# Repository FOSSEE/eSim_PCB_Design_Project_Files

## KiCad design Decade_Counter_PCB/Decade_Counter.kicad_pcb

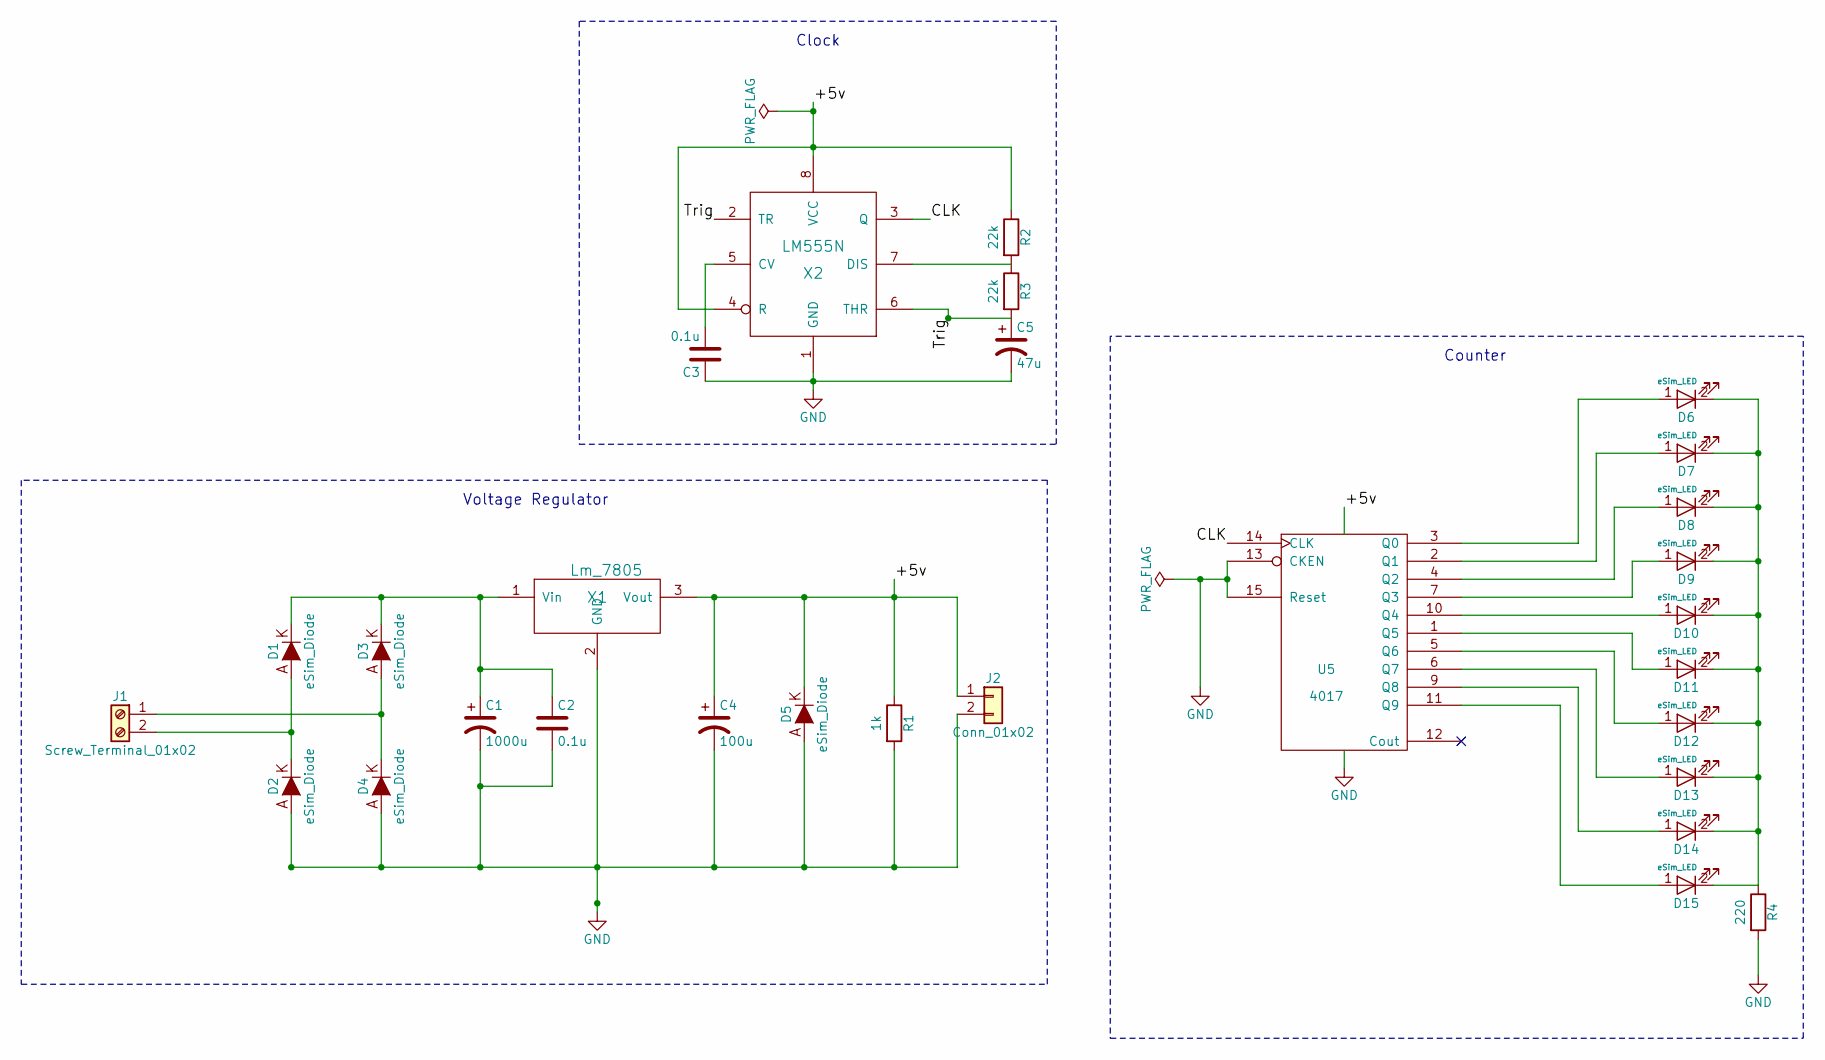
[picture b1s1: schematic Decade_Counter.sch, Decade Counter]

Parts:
C1: 1000u; CP_Radial_D5.0mm_P2.50mm
C2, C3: 0.1u; C_Disc_D3.0mm_W2.0mm_P2.50mm
C4: 100u; CP_Radial_D5.0mm_P2.50mm
C5: 47u; CP_Radial_D5.0mm_P2.50mm
D1, D2, D3, D4, D5: eSim_Diode; D_T-1_P5.08mm_Horizontal
D6, D7, D8, D9, D10, D11, D12, D13, D14, D15: eSim_LED; LED_D5.0mm
J1: Screw_Terminal_01x02; TerminalBlock_Altech_AK300-2_P5.00mm
J2: Conn_01x02; Pin_Header_Straight_1x02_Pitch2.54mm
R1: 1k; R_Axial_DIN0207_L6.3mm_D2.5mm_P10.16mm_Horizontal
R2, R3: 22k; R_Axial_DIN0207_L6.3mm_D2.5mm_P10.16mm_Horizontal
R4: 220; R_Axial_DIN0207_L6.3mm_D2.5mm_P10.16mm_Horizontal
U5: 4017; DIP-16_W7.62mm
X1: Lm_7805; TO-220-3_Vertical
X2: LM555N; DIP-8_W7.62mm

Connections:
/CLK: U5.14 (CLK), X2.3 (Q)
/Trig: C5.1, R3.2, X2.2 (TR), X2.6 (THR)
GND: C1.2, C2.2, C3.1, C4.2, C5.2, D2.1 (A), D4.1 (A), D5.1 (A), J2.2, R1.2, R4.2, U5.8 (VSS), U5.13 (CKEN), U5.15 (Reset), X1.2 (GND), X2.1 (GND)
unnamed: C1.1, C2.1, D1.2 (K), D3.2 (K), X1.1 (Vin)
unnamed: C3.2, X2.5 (CV)
unnamed: D1.1 (A), D2.2 (K), J1.2
unnamed: D3.1 (A), D4.2 (K), J1.1
unnamed: D6.1 (A), U5.3 (Q0)
unnamed: D7.1 (A), U5.2 (Q1)
unnamed: D8.1 (A), U5.4 (Q2)
unnamed: D9.1 (A), U5.7 (Q3)
unnamed: D10.1 (A), U5.10 (Q4)
unnamed: D6.2 (K), D7.2 (K), D8.2 (K), D9.2 (K), D10.2 (K), D11.2 (K), D12.2 (K), D13.2 (K), D14.2 (K), D15.2 (K), R4.1
unnamed: D11.1 (A), U5.1 (Q5)
unnamed: D12.1 (A), U5.5 (Q6)
unnamed: D13.1 (A), U5.6 (Q7)
unnamed: D14.1 (A), U5.9 (Q8)
unnamed: D15.1 (A), U5.11 (Q9)
unnamed: R2.2, R3.1, X2.7 (DIS)
VDD: C4.1, D5.2 (K), J2.1, R1.1, R2.1, U5.16 (VDD), X1.3 (Vout), X2.4 (R), X2.8 (VCC)

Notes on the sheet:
Voltage Regulator
Clock
Counter

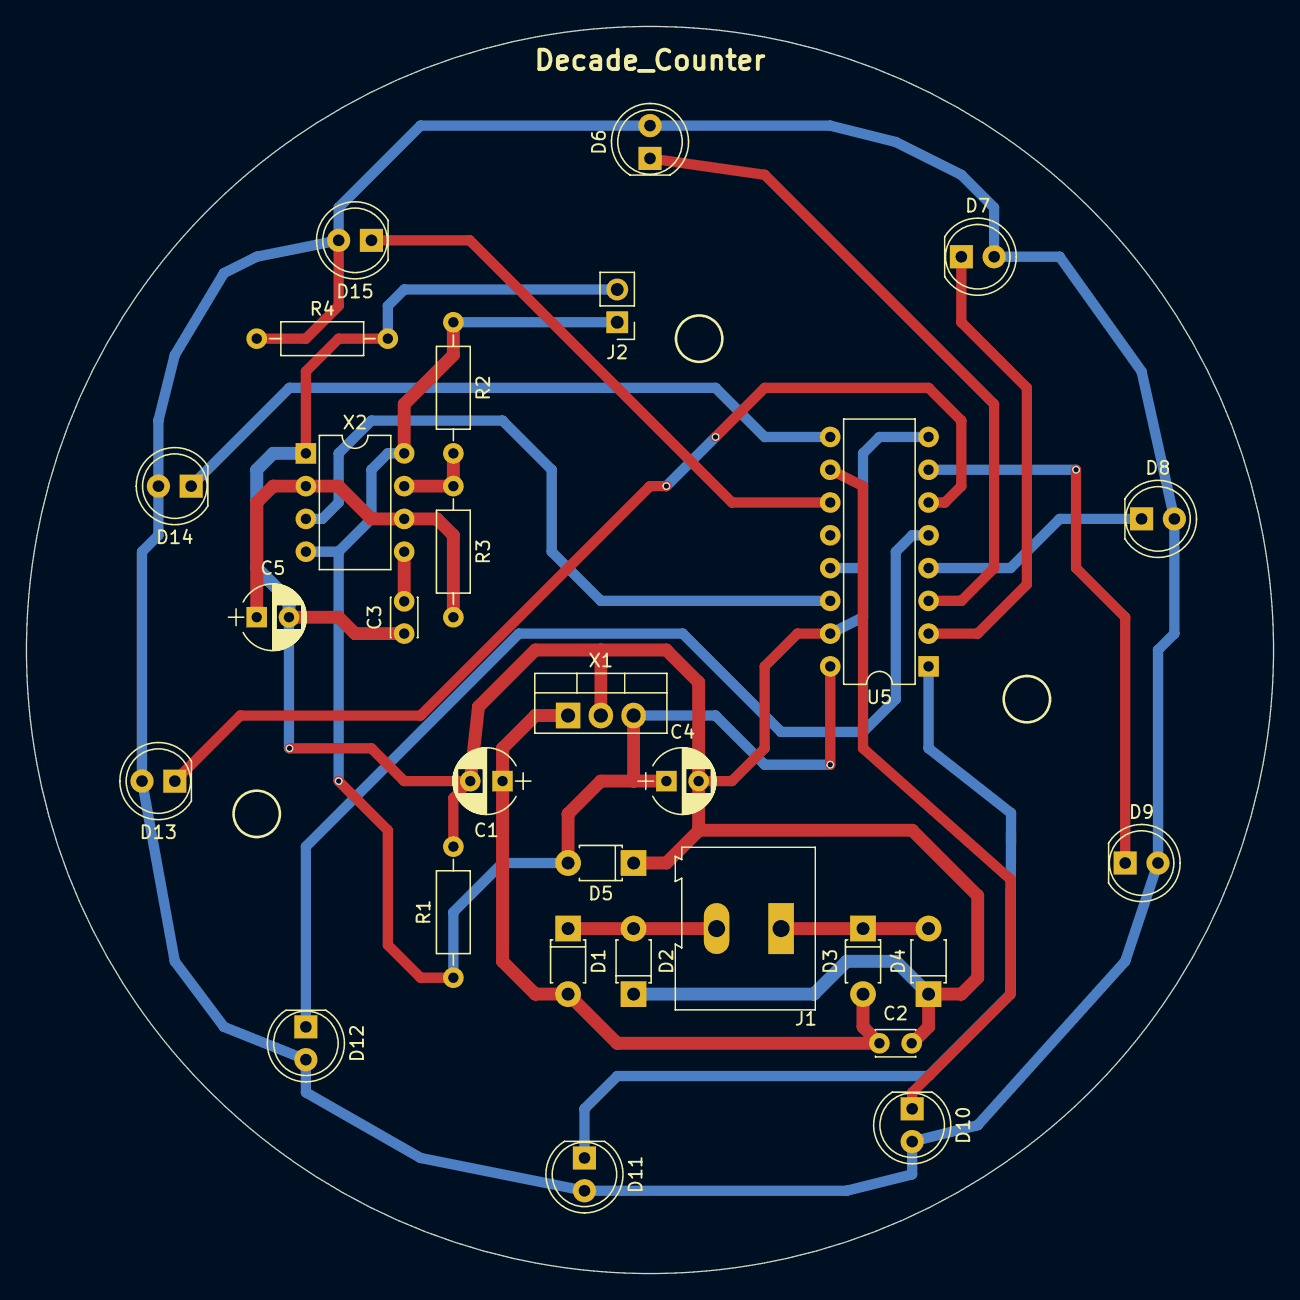
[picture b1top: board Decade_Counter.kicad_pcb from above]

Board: 2 copper layers, 96.7 x 96.7 mm, 29 parts (0 on the bottom side), 20 nets.

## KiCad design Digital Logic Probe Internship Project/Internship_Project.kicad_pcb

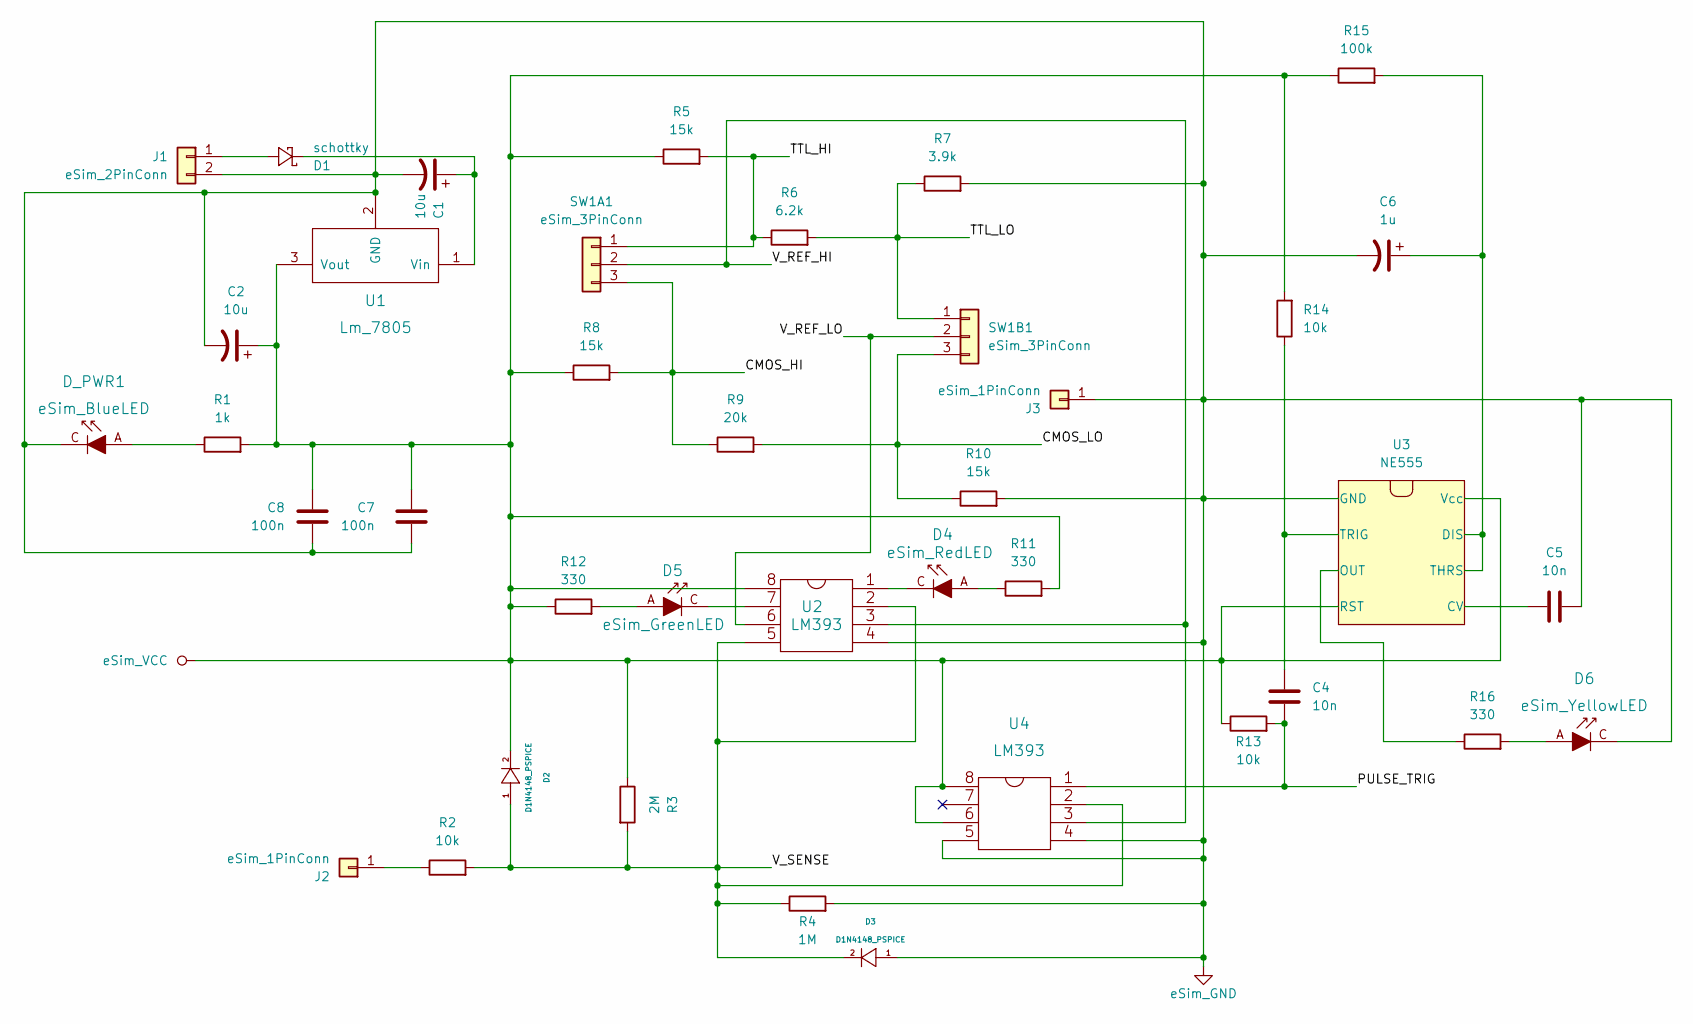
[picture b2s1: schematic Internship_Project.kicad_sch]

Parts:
C1, C2: 10u; CP_Radial_D5.0mm_P2.50mm
C4, C5: 10n; C_Disc_D5.0mm_W2.5mm_P5.00mm
C6: 1u; CP_Radial_D5.0mm_P2.50mm
C7, C8: 100n; C_Disc_D5.0mm_W2.5mm_P5.00mm
D1: schottky; D_DO-41_SOD81_P10.16mm_Horizontal
D2, D3: D1N4148_PSPICE; D_DO-35_SOD27_P7.62mm_Horizontal
D4: eSim_RedLED; LED_D5.0mm
D5: eSim_GreenLED; LED_D5.0mm
D6: eSim_YellowLED; LED_D5.0mm
D_PWR1: eSim_BlueLED; LED_D5.0mm
J1: eSim_2PinConn; PinHeader_1x02_P2.54mm_Vertical
J2, J3: eSim_1PinConn; PinHeader_1x01_P2.54mm_Vertical
R1: 1k; R_Axial_DIN0207_L6.3mm_D2.5mm_P10.16mm_Horizontal
R2, R13, R14: 10k; R_Axial_DIN0207_L6.3mm_D2.5mm_P10.16mm_Horizontal
R3: 2M; R_Axial_DIN0207_L6.3mm_D2.5mm_P10.16mm_Horizontal
R4: 1M; R_Axial_DIN0207_L6.3mm_D2.5mm_P10.16mm_Horizontal
R5, R8, R10: 15k; R_Axial_DIN0207_L6.3mm_D2.5mm_P10.16mm_Horizontal
R6: 6.2k; R_Axial_DIN0207_L6.3mm_D2.5mm_P10.16mm_Horizontal
R7: 3.9k; R_Axial_DIN0207_L6.3mm_D2.5mm_P10.16mm_Horizontal
R9: 20k; R_Axial_DIN0207_L6.3mm_D2.5mm_P10.16mm_Horizontal
R11, R12, R16: 330; R_Axial_DIN0207_L6.3mm_D2.5mm_P10.16mm_Horizontal
R15: 100k; R_Axial_DIN0207_L6.3mm_D2.5mm_P10.16mm_Horizontal
SW1A1, SW1B1: eSim_3PinConn; PinHeader_1x03_P2.54mm_Vertical
U1: Lm_7805; TO-220-3_Vertical
U2, U4: LM393; DIP-8_W7.62mm
U3: NE555; DIP-8_W7.62mm

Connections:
/CMOS_HI: R8.2, R9.1, SW1A1.3
/CMOS_LO: R9.2, R10.1, SW1B1.3
/PULSE_TRIG: C4.2, R13.2, U4.4 (1)
/TTL_HI: R5.2, R6.1, SW1A1.1
/TTL_LO: R6.2, R7.1, SW1B1.1
/V_REF_HI: SW1A1.2, U2.2 (3), U4.2 (3)
/V_REF_LO: SW1B1.2, U2.7 (6)
/V_SENSE: D2.1, D3.2, R2.2, R3.2, R4.1, U2.3 (2), U2.6 (5), U4.3 (2)
GND: C1.2, C2.2, C5.2, C6.2, C7.2, C8.2, D3.1, D6.C, D_PWR1.C, J1.2, J3.1, R4.2, R7.2, R10.2, U1.2 (GND), U2.5 (4), U3.1 (GND), U4.5 (4), U4.6 (5)
unnamed: C1.1, D1.2 (-), U1.1 (Vin)
unnamed: C4.1, R14.1, U3.2 (TRIG)
unnamed: C5.1, U3.5 (CV)
unnamed: C6.1, R15.2, U3.6 (THRS), U3.7 (DIS)
unnamed: D1.1 (+), J1.1
unnamed: D4.A, R11.1
unnamed: D4.C, U2.4 (1)
unnamed: D5.A, R12.2
unnamed: D5.C, U2.8 (7)
unnamed: D6.A, R16.2
unnamed: D_PWR1.A, R1.1
unnamed: J2.1, R2.1
unnamed: R16.1, U3.3 (OUT)
VCC: C2.1, C7.1, C8.1, D2.2, R1.2, R3.1, R5.1, R8.1, R11.2, R12.1, R13.1, R14.2, R15.1, U1.3 (Vout), U2.1 (8), U3.4 (RST), U3.8 (Vcc), U4.1 (8), U4.7 (6)

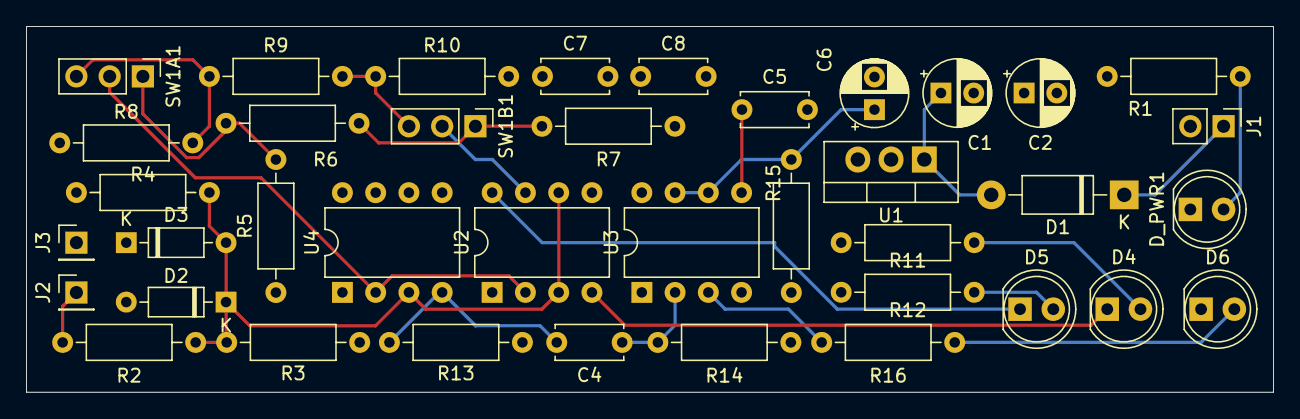
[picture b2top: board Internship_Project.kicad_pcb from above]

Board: 4 copper layers, 95.2 x 27.9 mm, 39 parts (0 on the bottom side), 23 nets.

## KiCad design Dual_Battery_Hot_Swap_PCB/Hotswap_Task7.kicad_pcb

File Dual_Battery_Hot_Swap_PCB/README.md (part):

# Dual-Battery Automatic Hot-Swap Circuit (2-Layer PCB)

A compact **Dual-Battery Automatic Hot-Swap Circuit** PCB designed for a **16 V, 5 A load** using **eSim 2.5 / KiCad 6.0.11**. The board connects two battery inputs (`J1_BAT1` and `J4_BAT2`) to a shared load output (`J3_LOAD1`) with voltage sensing, comparator control, MOSFET switching, and a bulk hold-up capacitor (`C4`) so power to the load stays smooth during battery switching.

**Author:** MD Hazijul Haque

**Program:** FOSSEE eSim Winter Internship 2026 (Task 7)

**Project Folder:** `Dual_Battery_Hot_Swap_PCB/` (`Hotswap_Task7`)

**Project Report:** [Hotswap_Task7_Report.pdf](https://github.com/Hazijul/eSim_PCB_Design_Hot_Swap_File/blob/main/Dual_Battery_Hot_Swap_PCB/Hotswap_Task7_Report.pdf)

**Repository & PR:** [Hazijul/eSim_PCB_Design_Hot_Swap_File](https://github.com/Hazijul/eSim_PCB_Design_Hot_Swap_File/tree/main/Dual_Battery_Hot_Swap_PCB) (`Dual_Battery_Hot_Swap_PCB/`) — [Pull Request #49 on FOSSEE/eSim_PCB_Design_Project_Files](https://github.com/FOSSEE/eSim_PCB_Design_Project_Files/pull/49)
---

## Hardware Specifications

| Parameter | Specification |
| :--- | :--- |
| **Voltage & Current Rating** | **16 V**, **5 A** load capability |
| **Battery Inputs** | Dual battery terminals (`J1_BAT1`, `J4_BAT2`) |
| **Load Output** | Shared load terminal (`J3_LOAD1`) |
| **Voltage Comparator** | **LM393** dual comparator (`U2A`, `U2B`, `U2C` power/ground) with **2.5 V** reference (`D1`) |
| **Power Switching MOSFETs** | Back-to-back P-channel MOSFETs (`Q1–Q4`, `Si4425BDY` / `AO3401A` in KiCad 6) |
| **Gate Drive MOSFETs** | N-channel MOSFET switches (`Q5–Q7`, `2N7002`) |
| **Hold-Up & Sense Parts** | **470 µF** bulk hold-up capacitor (`C4`), path/sense resistors (`R1`, `R2`), divider/bias network (`R4–R9`), indicators (`D2`, `D3`, `D4`, `R3`) |
| **PCB Stackup & Size** | **50 mm × 50 mm**, **2-Layer FR4** (`F.Cu` & `B.Cu`) |
| **Verification Tool** | eSim 2.5 / KiCad 6.0.11 (`ERC.rpt` & `DRC.rpt` with 0 errors) |

---

## Schematic Explanation

The schematic (`Hotswap_Task7.kicad_sch`) is divided into clear functional sections so anyone reading the circuit can see how battery inputs are sensed, how switching decisions are made, and how power reaches the load.

### 1. Dual Battery Inputs & Power Path
- **Two Battery Channels (`J1_BAT1` and `J4_BAT2`):** Two screw-terminal battery inputs feed into the hot-swap circuit so the system can draw from dual battery sources.
- **Series Resistors & Indicators (`R1`, `R2`, `D2`, `D3`):** Each battery branch includes its path/sense resistor (`R1`, `R2` at `1.0R`) and status LED (`D2`, `D3`) so you can tell at a glance which battery path is active or present.
- **Shared Load Output (`J3_LOAD1`):** Both battery paths feed into the main load output (`J3_LOAD1`) along with a load/status indicator branch (`R3` and `D4`).

### 2. Voltage Sensing & LM393 Comparator Logic
- **Reference & Voltage Divider (`D1`, `R4`, `R5`, `R6`):** A **2.5 V** reference (`D1`) and resistor divider network (`R4`, `R5`, `R6`) provide a steady comparison threshold and scaled voltage input (`COMP_IN+` / `COMP_IN-`) for monitoring battery voltage.
- **Comparator & Biasing (`U2A`, `U2B`, `U2C`, `R7`, `R8`, `R9`):** The **LM393** dual comparator compares the sensed voltage against the reference/threshold and drives the comparator output (`COMP_OUT`) with supporting bias and feedback resistors (`R7`, `R8`, `R9`).

### 3. Gate Drive & Back-to-Back MOSFET Switching
- **N-Channel Gate Drivers (`Q5–Q7`, `2N7002`):** The `2N7002` N-channel MOSFETs (`Q5`, `Q6`, `Q7`) act as small control switches driven by the comparator/logic signals (`COMP_OUT`, `COMP_INV`) to control the gate lines (`GATE1`, `GATE2`) of the main power MOSFETs.
- **Back-to-Back P-Channel MOSFETs (`Q1–Q4`):** Four P-channel MOSFETs (`Q1–Q2` on one path and `Q3–Q4` on the other) are arranged back-to-back. Using back-to-back MOSFETs blocks unwanted reverse current flow through the internal body diode when a channel is turned off or when one battery has a different voltage than the other.

### 4. Bulk Hold-Up Capacitor (`C4`)
- **Smoothing During Switchover:** A **470 µF** bulk capacitor (`C4`) sits on the output side toward the load (`J3_LOAD1`). When switching between battery sources or hot-swapping a pack, `C4` helps buffer brief current dips so the load sees a steadier voltage transition.

### Circuit Schematic

---

## PCB Design & Layout Explanation

The 2-layer PCB (`Hotswap_Task7.kicad_pcb`) fits everything into a compact **50 mm × 50 mm** square board while keeping high-current paths clear and organized.

### 1. Compact 50 mm × 50 mm Board Layout
- **Connectors & Accessibility:** Battery connectors (`J1_BAT1`, `J4_BAT2`) and the load output (`J3_LOAD1`) are placed cleanly around the board edges so wiring a 16 V, 5 A setup is straightforward.
- **Logical Grouping:** Power path components (`J1_BAT1`, `J4_BAT2`, `J3_LOAD1`, `Q1–Q4`, `R1`, `R2`, `C4`) sit close together along the high-current path, while the `LM393` comparator (`U2`), reference/divider resistors, and `2N7002` drivers (`Q5–Q7`) are grouped neatly nearby.

### 2. Handling 5 A Current Safely on a 2-Layer Board
A **5 A** load current on a 2-layer board requires wider, shorter copper paths than low-current signal traces:
- **Wider High-Current Copper:** The battery-to-MOSFET-to-load (`VOUT`) and ground return paths use wider traces/copper areas to reduce resistance, voltage drop, and heating at 5 A.
- **Short Loops:** Keeping `Q1–Q4`, `R1`/`R2`, and the `470 µF` capacitor (`C4`) close to `J1_BAT1`, `J4_BAT2`, and `J3_LOAD1` keeps high-current loops tight and tidy.

### 3. Separating Comparator & Gate Signals from High-Current Paths
- **Clean Sensing & Control:** Voltage-divider and comparator lines carry small reference/sense signals, while `Q5–Q7` drive `GATE1` and `GATE2`. Routing these cleanly away from heavy current paths reduces unwanted noise pickup.
- **Ground Reference:** A broad ground copper fill on the board gives return currents a low-resistance path and keeps reference measurements consistent.

### 4. Design Verification (ERC & DRC)
Two checks in eSim 2.5 / KiCad 6.0.11 verify the schematic and PCB before release:
- **Electrical Rules Check (`ERC.rpt`):** Confirms schematic connections and symbol references have **0 errors**.
- **Design Rules Check (`DRC.rpt`):** Confirms physical track widths, clearances, drill/pad rules, and copper pours on the 50 mm × 50 mm board pass with **0 errors**.

### Quick Summary of Circuit & Layout Blocks

| Block / Section | Key Parts | Role in the Circuit |
| :--- | :--- | :--- |
| **Battery & Load Terminals** | `J1_BAT1`, `J4_BAT2`, `J3_LOAD1` | Connects Battery 1, Battery 2, and the 16 V / 5 A load |
| **Voltage Sense & Comparator** | `LM393` (`U2`), `D1` (2.5 V), `R4–R9` | Monitors battery voltage against threshold/reference and drives control logic |
| **Gate Drive & Power Switches** | `Q1–Q4` (PMOS), `Q5–Q7` (`2N7002`), `R1`, `R2` | Switches battery paths smoothly with back-to-back reverse-blocking protection |
| **Hold-Up & Indicators** | `C4` (`470 µF`), `D2`, `D3`, `D4`, `R3` | Supports load voltage during switchover and shows status visually |

### 2-Layer PCB Layout (Front, Back & Both Layers)

### 3D PCB Render (Front & Back)

---

## Verification Results (ERC & DRC)

Both schematic ERC and PCB DRC were run and verified with **0 errors** in eSim 2.5 / KiCad 6.0.11, with full text reports saved as `ERC.rpt` and `DRC.rpt` inside this folder.

### Electrical Rules Check (ERC)

### Design Rules Check (DRC)

---

## System Working Flow

```mermaid
flowchart TD
    subgraph Inputs["Dual Battery Inputs"]
        B1["Battery 1 (J1_BAT1)<br/>R1 (1.0R) & Indicator D2"]
        B2["Battery 2 (J4_BAT2)<br/>R2 (1.0R) & Indicator D3"]
    end

    subgraph Control["Voltage Sense & Comparator Control"]
        SENSE["Voltage Divider & 2.5V Ref<br/>(D1, R4, R5, R6)"] --> CMP["LM393 Dual Comparator (U2)<br/>& Bias/Feedback (R7, R8, R9)"]
        CMP --> DRV["2N7002 Gate Drivers (Q5–Q7)<br/>GATE1 & GATE2 Control"]
    end

    B1 -. "Voltage Sensing" .-> SENSE
    B2 -. "Voltage Sensing" .-> SENSE

    subgraph Switching["Back-to-Back PMOS Hot-Swap Stage"]
        B1 --> PMOS1["Q1–Q2 Back-to-Back PMOS<br/>(Si4425BDY / AO3401A)"]
        B2 --> PMOS2["Q3–Q4 Back-to-Back PMOS<br/>(Si4425BDY / AO3401A)"]
        DRV -. "Gate Drive" .-> PMOS1
        DRV -. "Gate Drive" .-> PMOS2
    end

    subgraph Output["Hold-Up & Load Output (16V, 5A)"]
        PMOS1 --> BUS["Common Output Bus"]
        PMOS2 --> BUS
        BUS --> CAP["470 µF Bulk Hold-Up Cap (C4)"]
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
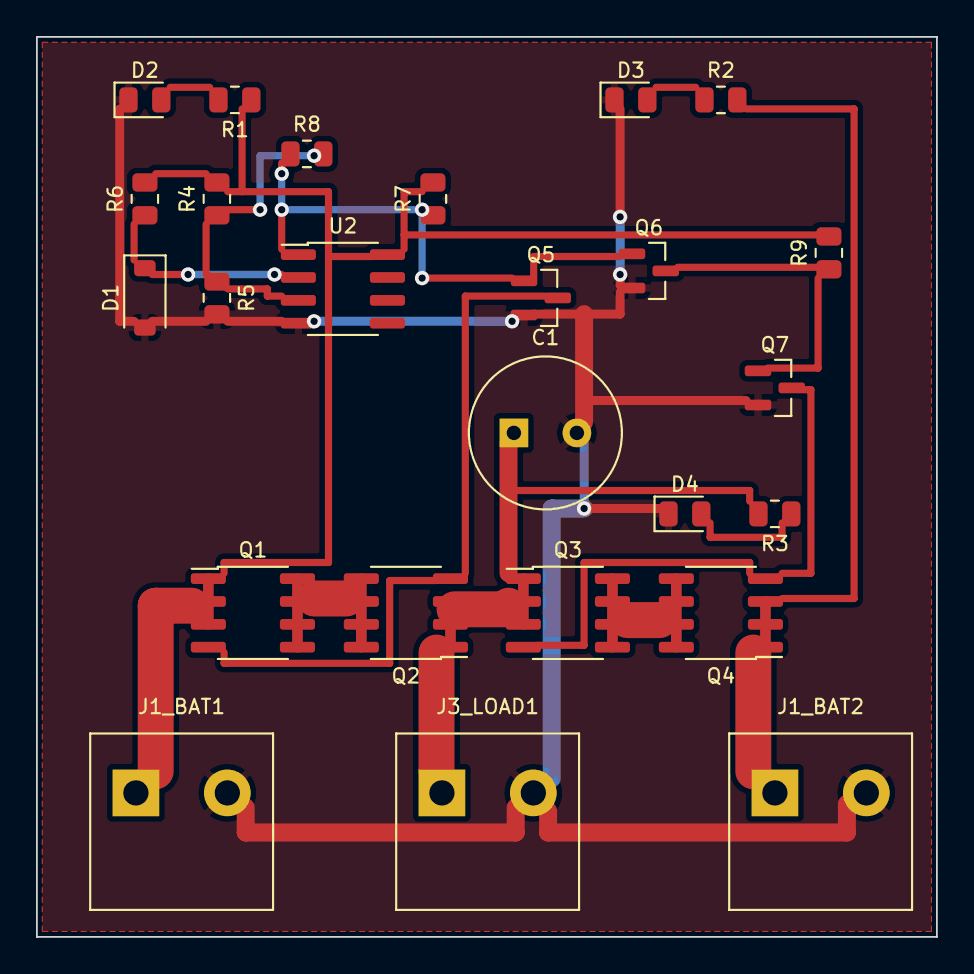
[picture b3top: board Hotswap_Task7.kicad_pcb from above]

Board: 2 copper layers, 50.0 x 50.0 mm, 25 parts (0 on the bottom side), 15 nets.

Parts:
C1: 470uF; CP_Radial_D8.0mm_P3.50mm
D1: 2.5V; D_SOD-123
D2, D3, D4: LED; LED_0805_2012Metric
J1_BAT1, J1_BAT2, J3_LOAD1: Screw_Terminal_01x02; TerminalBlock_Phoenix_MKDS-1,5-2-5.08_1x02_P5.08mm_Horizont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
Q1, Q2, Q3, Q4: Si4425BDY; SOIC-8_3.9x4.9mm_P1.27mm
Q5, Q6, Q7: 2N7002; SOT-23
R1, R2, R3: 1.8k; R_0805_2012Metric
R4: 49.9k; R_0805_2012Metric
R5, R6, R7, R9: 10k; R_0805_2012Metric
R8: 1.1Meg; R_0805_2012Metric
U2: LM393; SOIC-8_3.9x4.9mm_P1.27mm

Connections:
COMP_IN+: R4.1, R5.2, R8.2, U2.3
COMP_IN-: D1.1, R6.1, U2.2
COMP_INV: Q6.3, Q7.1, R9.1
COMP_OUT: Q5.1, Q6.1, R7.1, R8.1, U2.1
GATE1: Q1.4, Q2.4, Q5.3
GATE2: Q3.4, Q4.4, Q7.3
GND: C1.2, D1.2, D2.1, D3.1, D4.1, J1_BAT1.2, J1_BAT2.2, J3_LOAD1.2, Q5.2, Q6.2, Q7.2, R5.1, U2.4
unnamed: D2.2, R1.2
unnamed: D3.2, R2.1
unnamed: D4.2, R3.1
unnamed: Q1.5, Q1.6, Q1.7, Q1.8, Q2.5, Q2.6, Q2.7, Q2.8
unnamed: Q3.5, Q3.6, Q3.7, Q3.8, Q4.5, Q4.6, Q4.7, Q4.8
VOUT: C1.1, J3_LOAD1.1, Q2.1, Q2.2, Q2.3, Q3.1, Q3.2, Q3.3, R3.2
V_BAT1: J1_BAT1.1, Q1.1, Q1.2, Q1.3, R1.1, R4.2, R6.2, R7.2, R9.2, U2.8
V_BAT2: J1_BAT2.1, Q4.1, Q4.2, Q4.3, R2.2

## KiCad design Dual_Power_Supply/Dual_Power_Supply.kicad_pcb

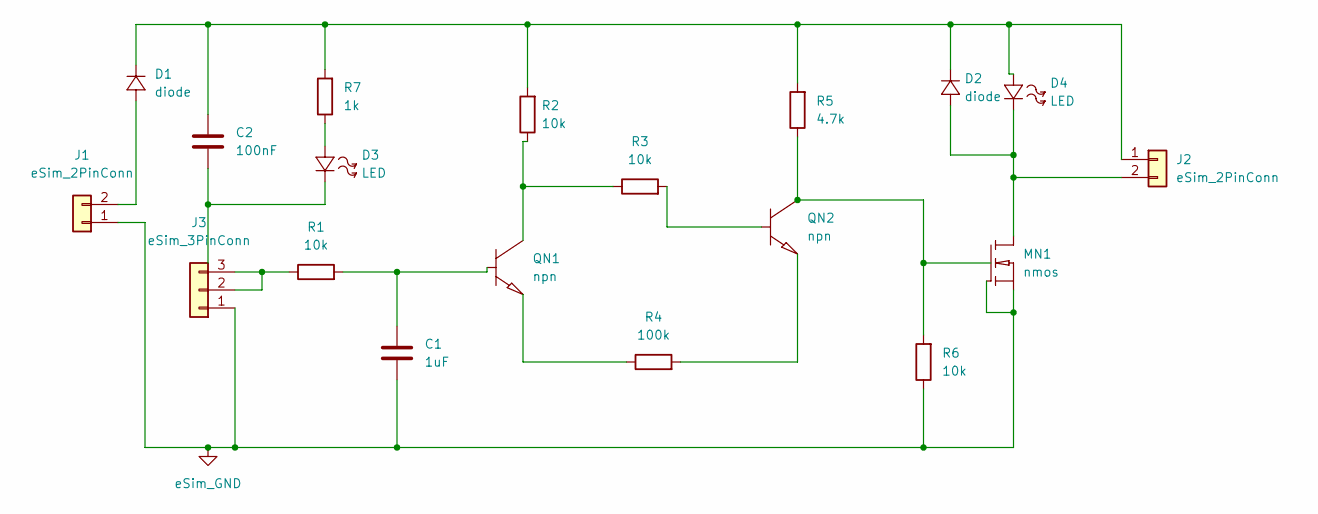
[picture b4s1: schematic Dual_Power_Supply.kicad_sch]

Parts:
C1: 1uF; C_Disc_D5.0mm_W2.5mm_P5.00mm
C2: 100nF; C_Disc_D5.0mm_W2.5mm_P5.00mm
D1, D2: diode; D_DO-41_SOD81_P10.16mm_Horizontal
D3, D4: LED; LED_D5.0mm
J1, J2: eSim_2PinConn; PinHeader_1x02_P2.54mm_Vertical
J3: eSim_3PinConn; PinHeader_1x03_P2.54mm_Vertical
MN1: nmos; TO-220-3_Vertical
QN1, QN2: npn; TO-92_Inline
R1, R2, R3, R6: 10k; R_Axial_DIN0207_L6.3mm_D2.5mm_P10.16mm_Horizontal
R4: 100k; R_Axial_DIN0207_L6.3mm_D2.5mm_P10.16mm_Horizontal
R5: 4.7k; R_Axial_DIN0207_L6.3mm_D2.5mm_P10.16mm_Horizontal
R7: 1k; R_Axial_DIN0207_L6.3mm_D2.5mm_P10.16mm_Horizontal

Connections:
GND: C1.2, J1.1, J3.1, MN1.2 (G), MN1.3 (S), R6.1
unnamed: D3.1 (+), R7.1
unnamed: C2.2, D3.2 (-)
unnamed: D2.1 (+), D4.2 (-), J2.2, MN1.1 (D)
unnamed: D1.1 (+), J1.2
unnamed: QN1.3 (E), R4.1
unnamed: QN2.1 (C), R5.1, R6.2
unnamed: QN2.3 (E), R4.2
unnamed: J3.2, J3.3, R1.1
unnamed: C1.1, QN1.2 (B), R1.2
unnamed: QN1.1 (C), R2.1, R3.1
unnamed: QN2.2 (B), R3.2
unnamed: C2.1, D1.2 (-), D2.2 (-), D4.1 (+), J2.1, R2.2, R5.2, R7.2

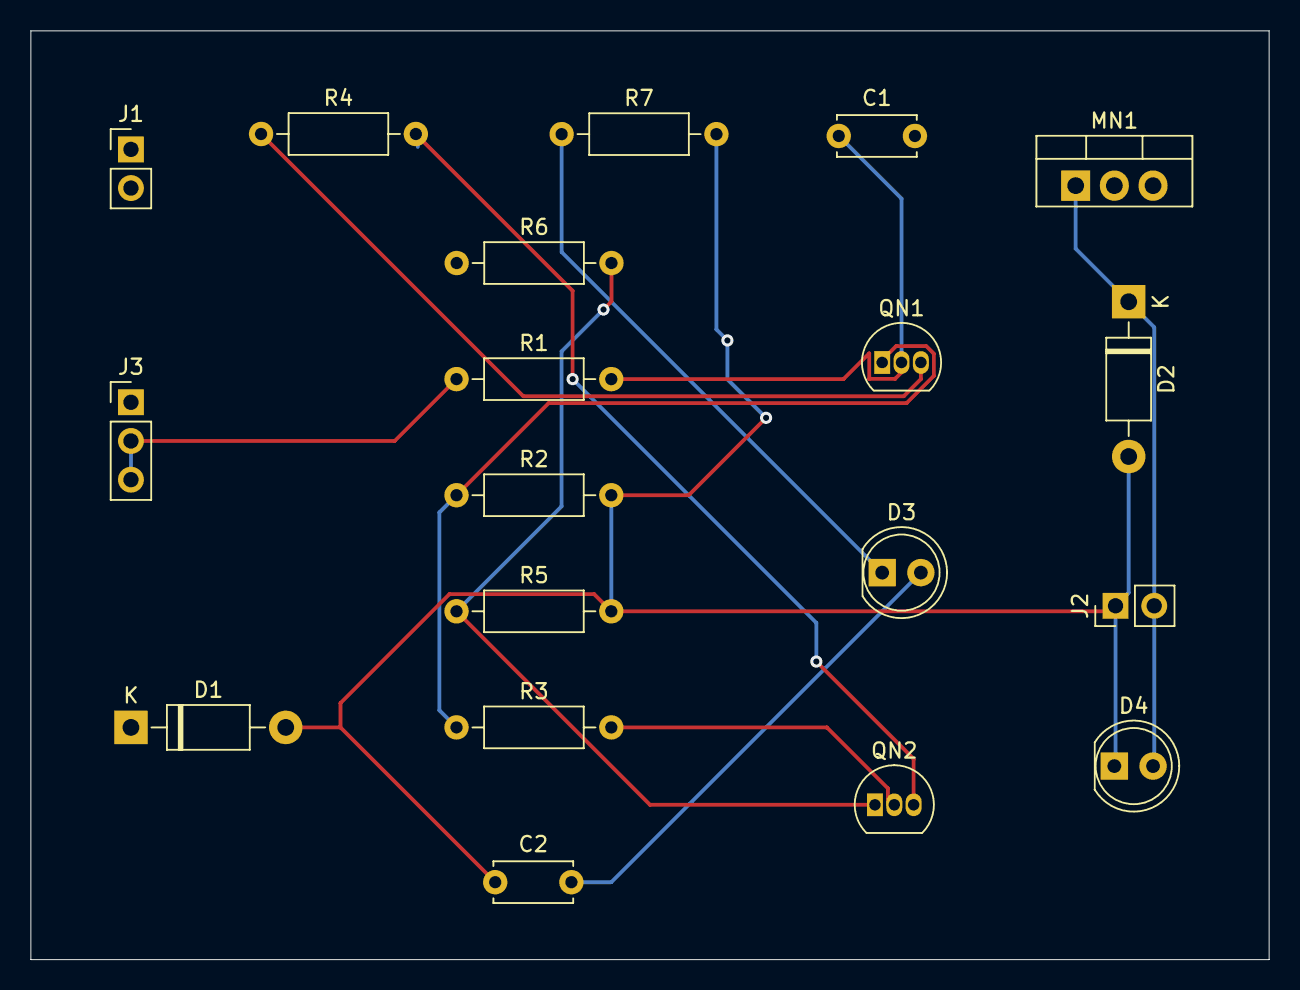
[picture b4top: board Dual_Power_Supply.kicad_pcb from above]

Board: 4 copper layers, 81.3 x 61.0 mm, 19 parts (0 on the bottom side), 13 nets.

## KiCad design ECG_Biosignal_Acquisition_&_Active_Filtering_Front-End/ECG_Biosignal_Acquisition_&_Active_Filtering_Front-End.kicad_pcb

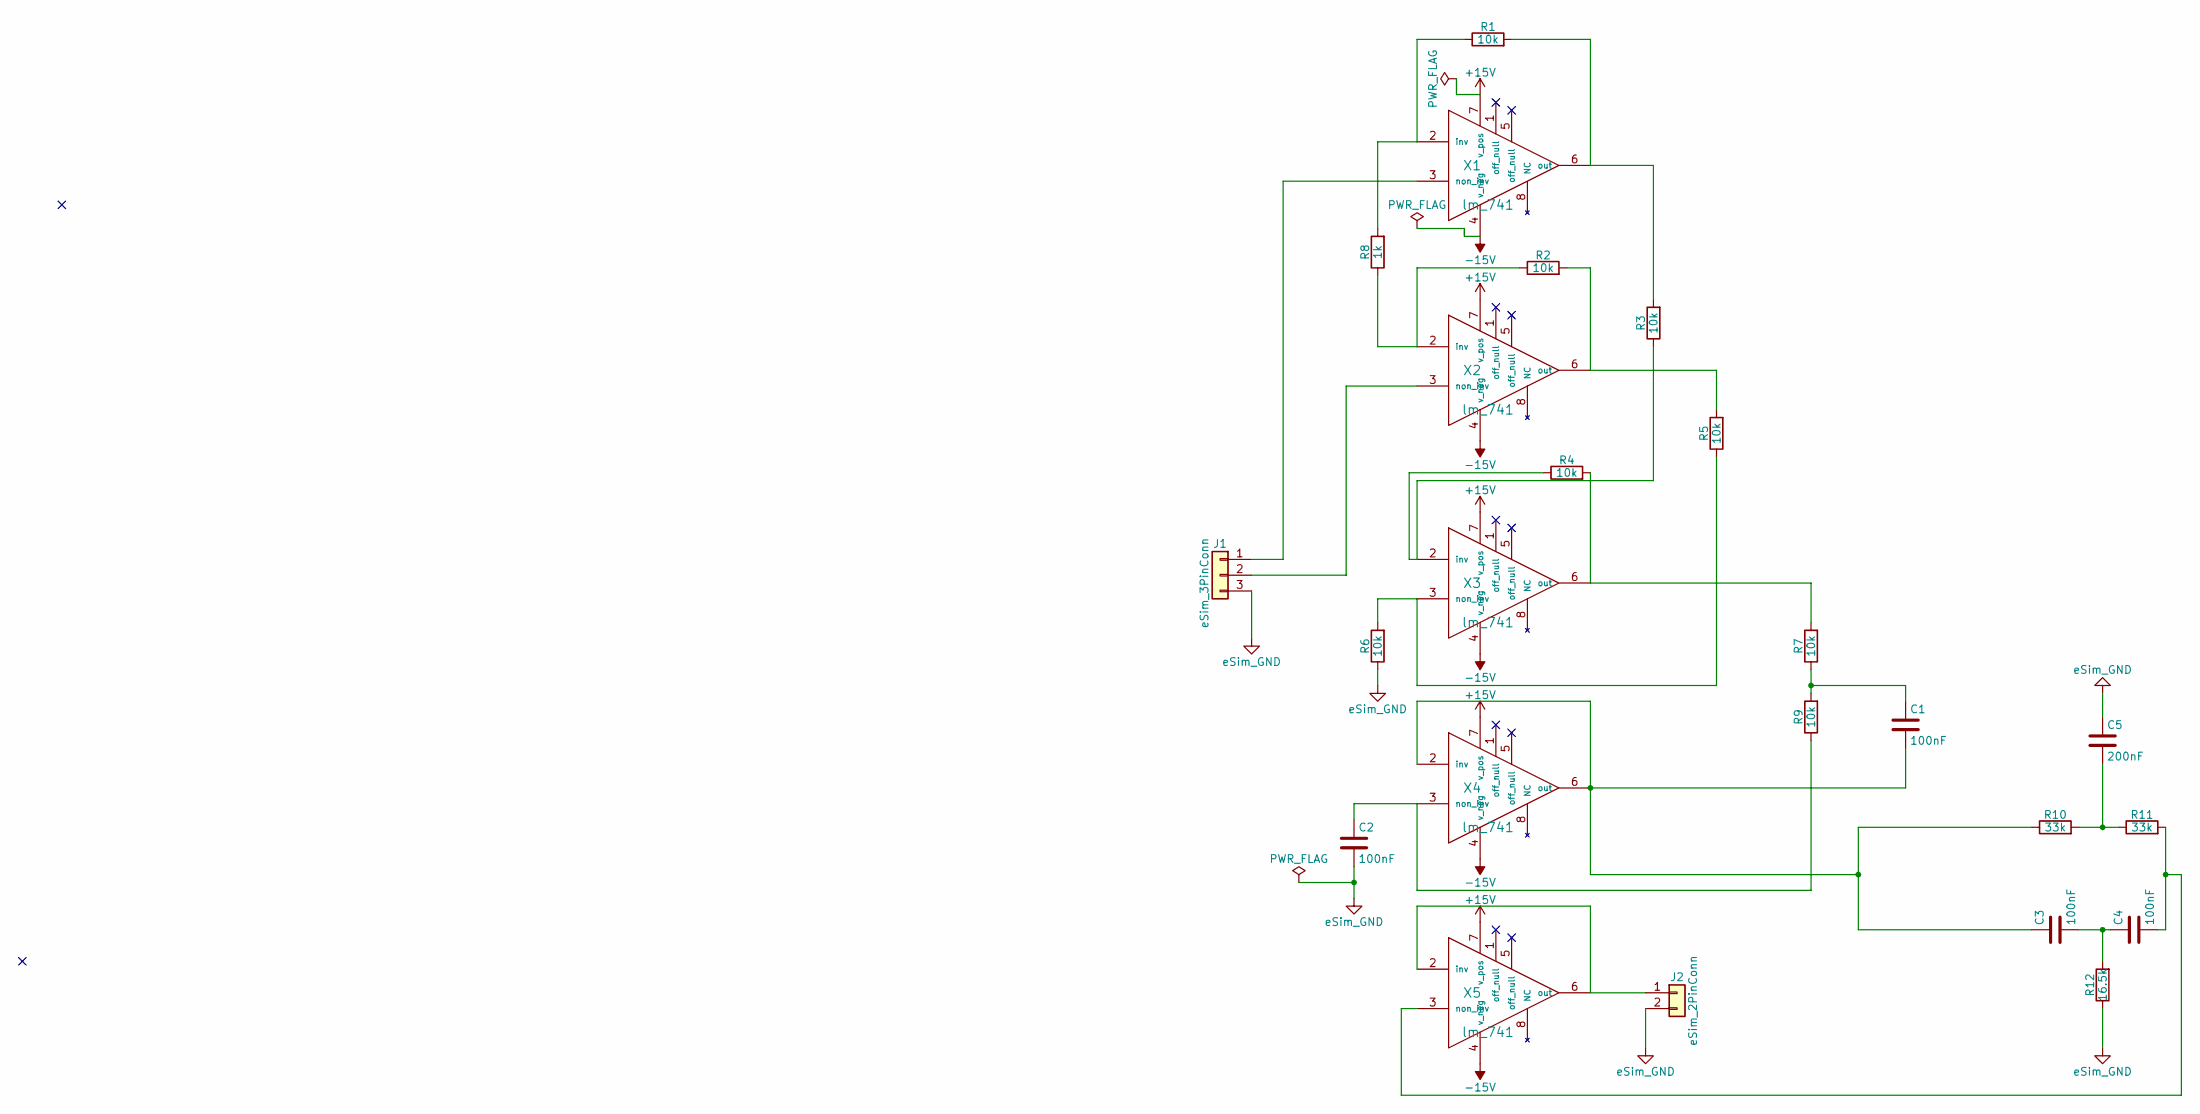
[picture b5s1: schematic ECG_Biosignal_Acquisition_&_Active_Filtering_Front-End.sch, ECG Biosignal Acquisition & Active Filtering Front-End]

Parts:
C1, C2, C3, C4: 100nF; C_Disc_D5.0mm_W2.5mm_P5.00mm
C5: 200nF; C_Disc_D5.0mm_W2.5mm_P5.00mm
J1: eSim_3PinConn; Pin_Header_Straight_1x03_Pitch2.54mm
J2: eSim_2PinConn; Pin_Header_Straight_1x02_Pitch2.54mm
R1, R2, R3, R4, R5, R6, R7, R9: 10k; R_Axial_DIN0207_L6.3mm_D2.5mm_P7.62mm_Horizontal
R8: 1k; R_Axial_DIN0207_L6.3mm_D2.5mm_P7.62mm_Horizontal
R10, R11: 33k; R_Axial_DIN0207_L6.3mm_D2.5mm_P7.62mm_Horizontal
R12: 16.5k; R_Axial_DIN0207_L6.3mm_D2.5mm_P7.62mm_Horizontal
X1, X2, X3, X4, X5: lm_741; DIP-8_W7.62mm

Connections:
+15V: X1.7 (v_pos), X2.7 (v_pos), X3.7 (v_pos), X4.7 (v_pos), X5.7 (v_pos)
-15V: X1.4 (v_neg), X2.4 (v_neg), X3.4 (v_neg), X4.4 (v_neg), X5.4 (v_neg)
GND: C2.2, C5.1, J1.3, J2.2, R6.1, R12.1
unnamed: C1.1, R7.1, R9.2
unnamed: C1.2, C3.1, R10.1, X4.2 (inv), X4.6 (out)
unnamed: C2.1, R9.1, X4.3 (non_inv)
unnamed: C3.2, C4.1, R12.2
unnamed: C4.2, R11.2, X5.3 (non_inv)
unnamed: C5.2, R10.2, R11.1
unnamed: J1.1, X1.3 (non_inv)
unnamed: J1.2, X2.3 (non_inv)
unnamed: J2.1, X5.2 (inv), X5.6 (out)
unnamed: R1.1, R8.2, X1.2 (inv)
unnamed: R1.2, R3.2, X1.6 (out)
unnamed: R2.1, R8.1, X2.2 (inv)
unnamed: R2.2, R5.2, X2.6 (out)
unnamed: R3.1, R4.1, X3.2 (inv)
unnamed: R4.2, R7.2, X3.6 (out)
unnamed: R5.1, R6.2, X3.3 (non_inv)

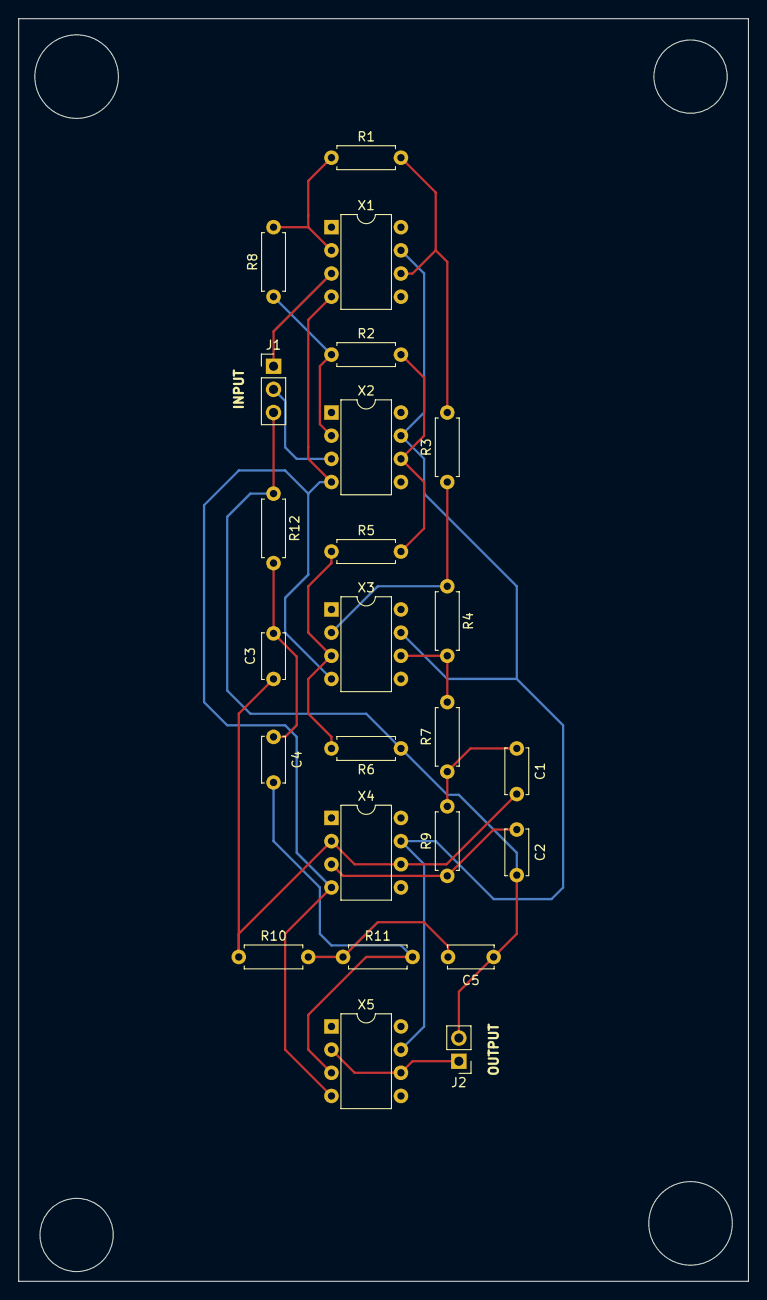
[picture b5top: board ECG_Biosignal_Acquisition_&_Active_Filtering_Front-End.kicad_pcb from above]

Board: 6 copper layers, 80.0 x 138.4 mm, 24 parts (0 on the bottom side), 19 nets.

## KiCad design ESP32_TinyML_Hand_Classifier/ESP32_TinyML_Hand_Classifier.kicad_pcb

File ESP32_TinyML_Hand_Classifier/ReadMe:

# ESP32-CAM TinyML Carrier Board

A custom dual-layer PCB designed in KiCad to carry an ESP32-CAM module for real-time, edge-deployed TinyML inference — built for a hand-sign classifier project.

## Overview

Breadboards work fine for early prototyping, but they fall short once you need stable power delivery and reliable RF performance for a camera-based inference workload running at the edge. This board was designed from scratch — schematic, custom footprints, routing, and manufacturing outputs — to solve that.

## Features

- **Fully custom schematic**, built from the ground up
- **Custom-built footprints** for most components, including the ESP32-CAM module itself
- **AMS1117 3.3V regulator** with dedicated 0.8mm high-current power traces for stable camera power under inference load
- **0.4mm signal traces** for data/control lines
- **Onboard reset pushbuttons** and I2C expansion headers
- **Antenna keepout zone** to protect Wi-Fi RF performance
- **Final DRC: 0 errors**

## Hardware Summary

| Component | Function |
|---|---|
| U2 (ESP32-CAM) | Main compute + camera module |
| U1 (AMS1117-3.3V) | Voltage regulation |
| J1 | Power input (terminal block) |
| J2, J3 | I2C / expansion headers |
| SW1, SW2 | Pushbuttons (e.g. reset / user input) |
| D1 | Status LED |
| R1–R5, C1–C4 | Supporting passives (pull-ups, decoupling, filtering) |

## Repository Structure

```
.
├── hardware/
│   ├── project.kicad_pro       # KiCad project file
│   ├── project.kicad_sch       # Schematic
│   ├── project.kicad_pcb       # PCB layout
│   └── libs/
│       ├── esp32cam.pretty/    # Custom footprint library (required)
│       └── symbols/            # Custom symbol library (if any)
├── gerbers/                    # Fabrication outputs (Gerber + Excellon drill files)
├── docs/
│   └── images/                 # Renders, screenshots for documentation
└── README.md
```

## Getting Started

### Requirements
- [KiCad](https://www.kicad.org/) 6.0 or later

### Opening the project
1. Clone the repo:
   ```bash
   git clone https://github.com/<your-username>/<repo-name>.git
   ```
2. **Register the custom footprint library** before opening the PCB:
   - In KiCad, go to **Preferences → Manage Footprint Libraries**
   - Add `hardware/libs/esp32cam.pretty` as a project-specific library
   - This step is required — without it, KiCad will report `footprint 'esp32cam:esp32' not found` when loading the board.
3. Open `hardware/project.kicad_pro`.

### Manufacturing
Gerber and Excellon drill files are pre-generated in `/gerbers` and are ready to submit to a fab house (e.g. JLCPCB, PCBWay).

## Design Notes

**Power delivery:** The ESP32-CAM's onboard regulation isn't rated for sustained current draw during camera inference. A dedicated AMS1117 3.3V regulator with 0.8mm traces was added to ensure clean, stable power under load.

**Antenna keepout:** A Rule Area is defined over the ESP32-CAM's antenna region to block copper pours, tracks, and vias in that zone, protecting Wi-Fi performance. When editing this Rule Area, always explicitly select target layers (F.Cu / B.Cu) in its properties — leaving the layer selection empty while keepout rules are enabled causes KiCad to apply the block inconsistently, which can silently prevent routing across the entire board rather than just the intended region.

## Status

- [x] Schematic complete
- [x] Custom footprints created
- [x] Routing complete
- [x] DRC clean (0 errors)
- [x] Gerbers generated
- [ ] Assembly & bring-up testing
- [ ] Firmware integration

## License

Open sourced.

## Acknowledgments

Built using [KiCad](https://www.kicad.org/), an open-source EDA suite.

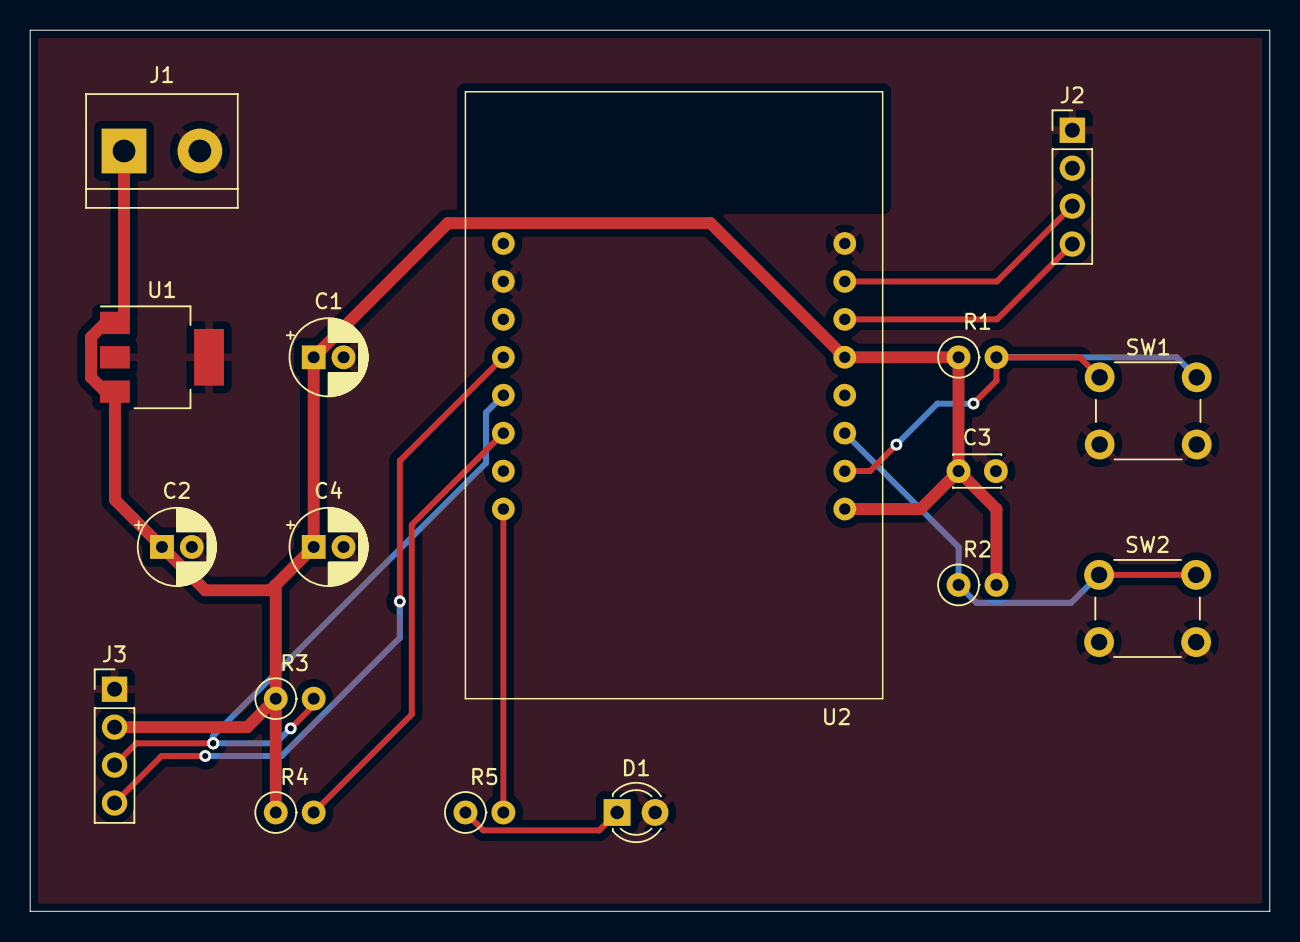
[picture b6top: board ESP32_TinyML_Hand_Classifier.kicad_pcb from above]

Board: 2 copper layers, 83.0 x 59.0 mm, 17 parts (0 on the bottom side), 11 nets.

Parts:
C1, C2: 10uF; CP_Radial_D5.0mm_P2.00mm
C3: 100nF; C_Disc_D3.0mm_W2.0mm_P2.50mm
C4: 1000uF; CP_Radial_D5.0mm_P2.00mm
D1: eSim_LED; LED_D3.0mm
J1: CONN_2; TerminalBlock_bornier-2_P5.08mm
J2, J3: CONN_4; PinHeader_1x04_P2.54mm_Vertical
R1, R2: 10k; R_Axial_DIN0207_L6.3mm_D2.5mm_P2.54mm_Vertical
R3, R4: 4.7k; R_Axial_DIN0207_L6.3mm_D2.5mm_P2.54mm_Vertical
R5: 330; R_Axial_DIN0207_L6.3mm_D2.5mm_P2.54mm_Vertical
SW1, SW2: PUSHBUTTON_2; SW_PUSH_6mm
U1: AMS1117_3V3; SOT-223-3_TabPin2
U2: esp32cam; esp32

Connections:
GND: C1.2, C2.2, C3.2, C4.2, D1.2 (K), J1.2 (GND), J2.1 (PIN_A), J3.1 (PIN_A), SW1.2 (PIN_B), SW2.2 (PIN_B), U1.2 (GND), U2.2 (GND), U2.16 (GND)
unnamed: D1.1 (A), R5.1
unnamed: J3.4 (PIN_D), U2.4 (GPIO13)
unnamed: R1.2, SW1.1 (PIN_A), U2.10 (EN)
unnamed: R2.1, SW2.1 (PIN_A), U2.11 (GPIO0)
unnamed: J3.3 (PIN_C), R3.2, U2.5 (GPIO15)
unnamed: R5.2, U2.8 (GPIO4)
unnamed: R4.2, U2.6 (GPIO14)
unnamed: J2.4 (PIN_D), U2.14 (U0RXD)
unnamed: J2.3 (PIN_C), U2.15 (U0TXD)
VCC: C1.1, C2.1, C3.1, C4.1, J1.1 (VIN), J3.2 (PIN_B), R1.1, R2.2, R3.1, R4.1, U1.1 (VI), U1.3 (VO), U2.9 (3V3), U2.13 (VCC)
